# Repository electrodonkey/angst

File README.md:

# ANGST - Angle seNsor Gimbal SysTem

## Master thesis project in Advanced Microelectronics

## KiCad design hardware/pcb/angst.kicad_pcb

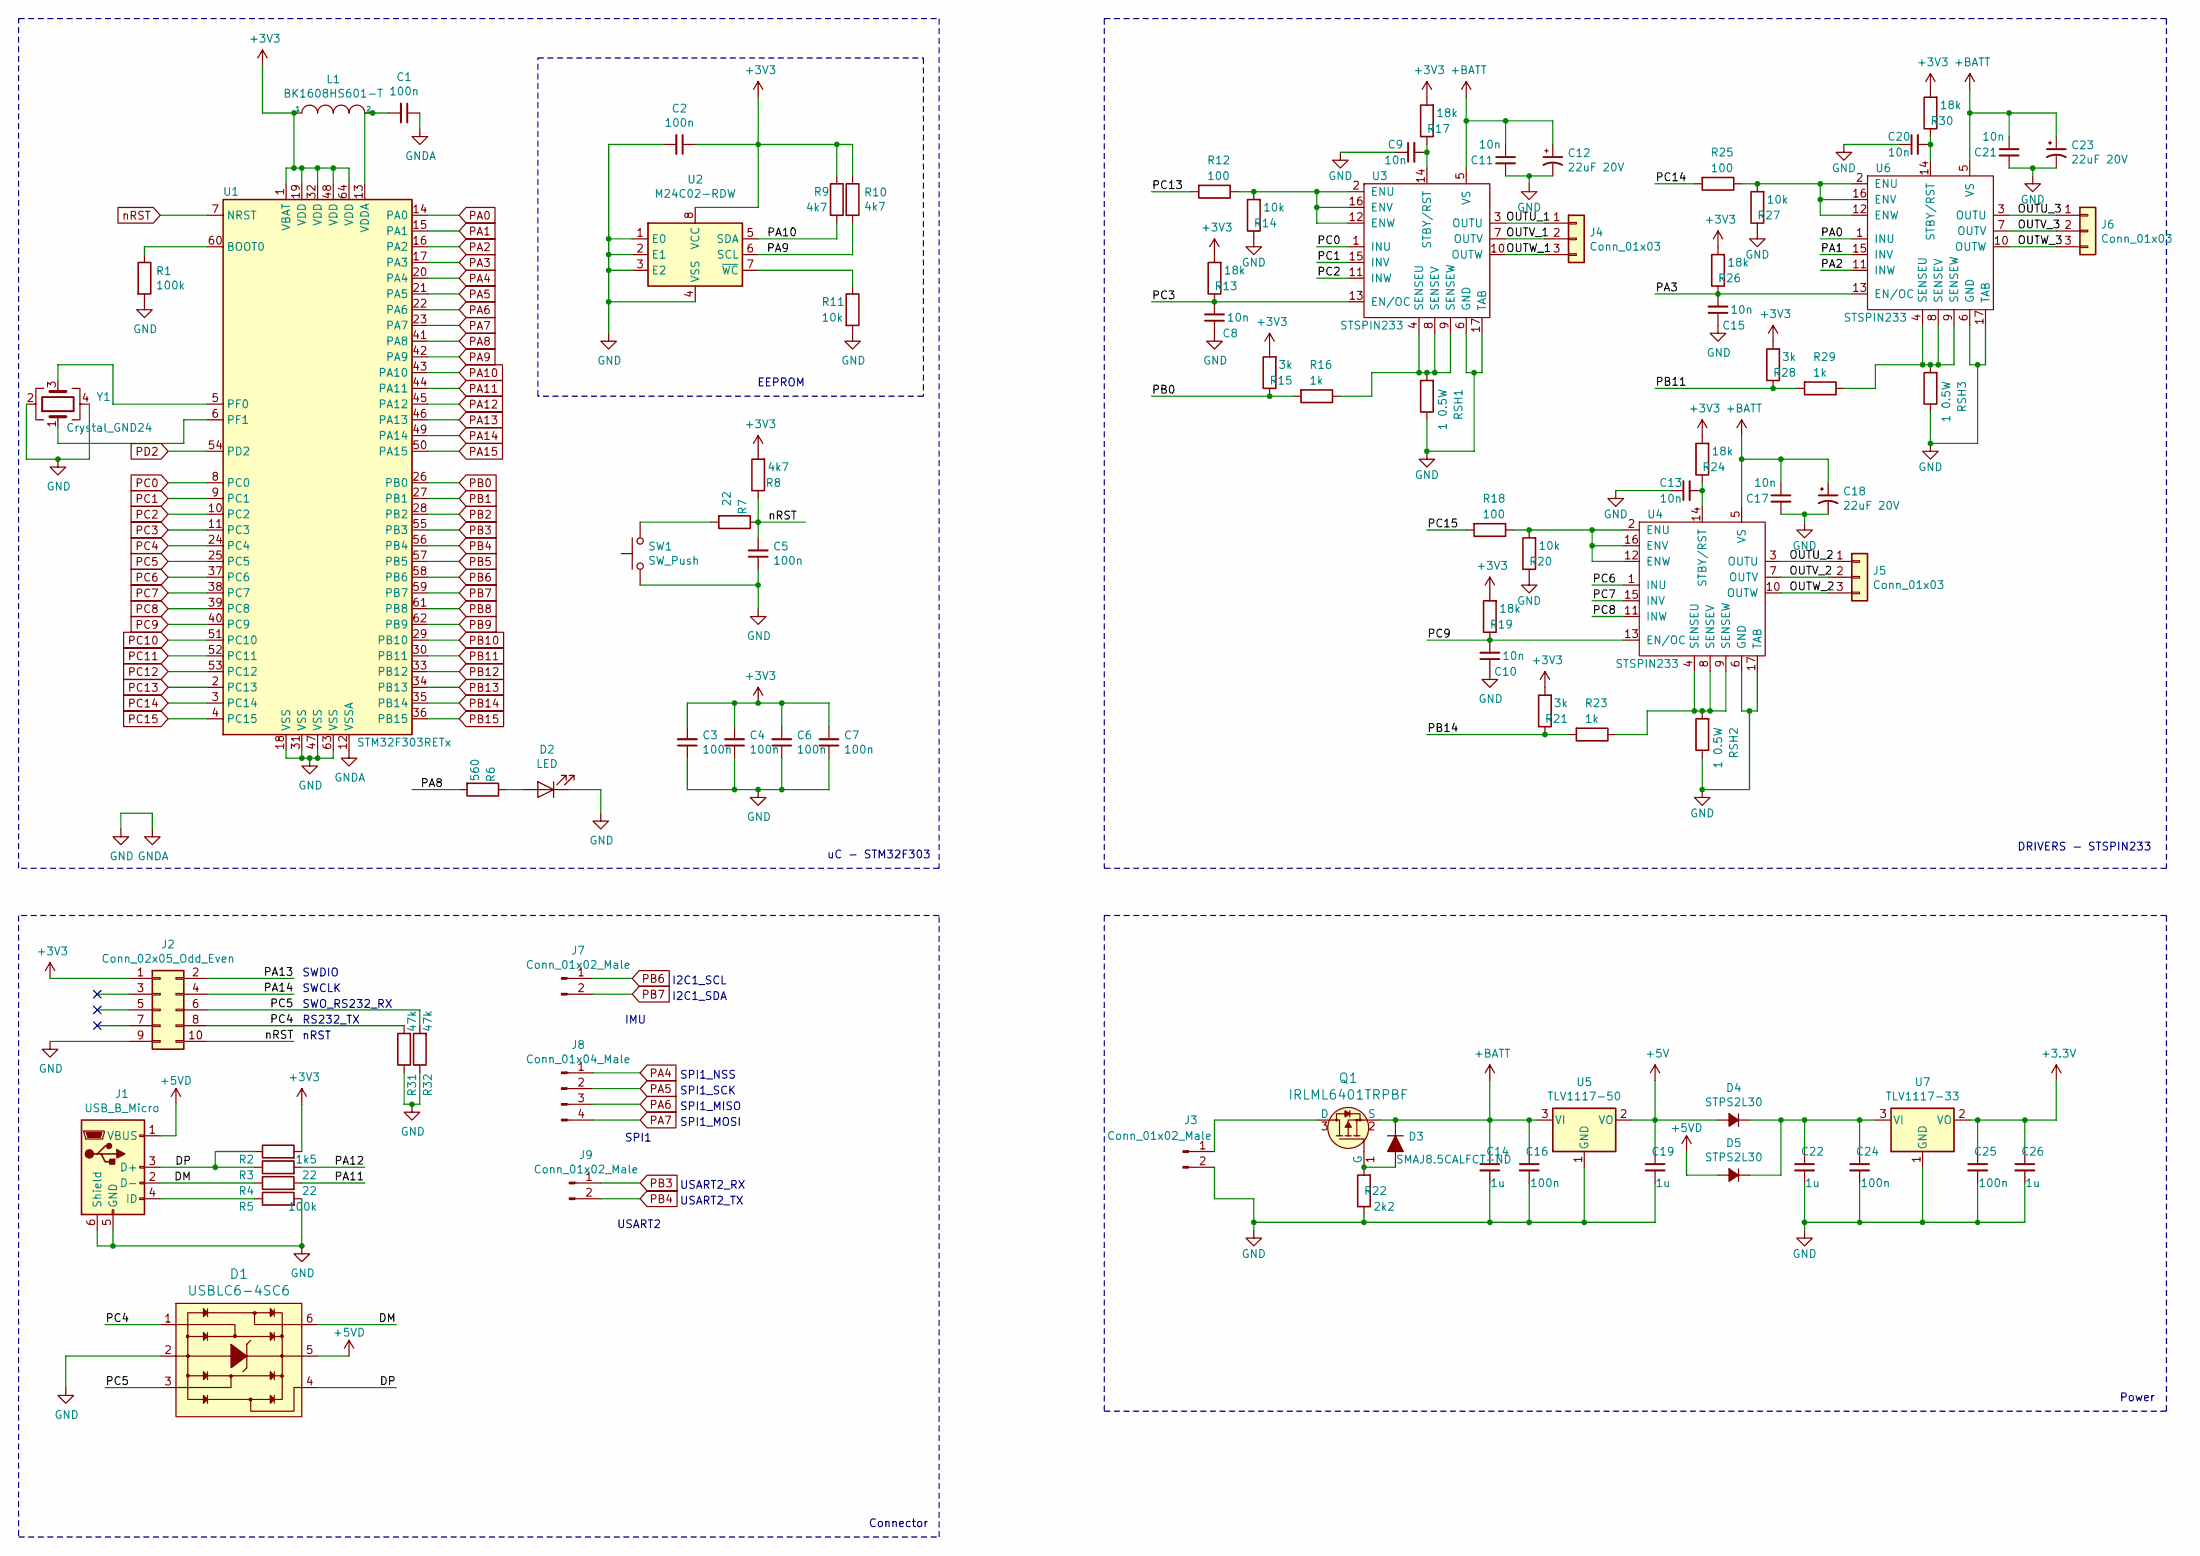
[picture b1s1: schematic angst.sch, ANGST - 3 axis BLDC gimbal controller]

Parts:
C1, C2, C3, C4, C5, C6, C7, C16, C24, C25: 100n; C_0603_1608Metric_Pad1.05x0.95mm_HandSolder
C8, C9, C10, C11, C13, C15, C17, C20, C21: 10n; C_0603_1608Metric_Pad1.05x0.95mm_HandSolder
C12, C18, C23: 22uF 20V; CP_EIA-1608-08_AVX-J_Pad1.25x1.05mm_HandSolder
C14, C19, C22, C26: 1u; C_0603_1608Metric_Pad1.05x0.95mm_HandSolder
D1: USBLC6-4SC6; SOT23-6L; MPN USBLC6-4SC6; Digi-Key_PN 497-4492-1-ND
D2: LED; LED_0603_1608Metric_Pad1.05x0.95mm_HandSolder
D3: SMAJ8.5CALFCT-ND; D_SMA
D4, D5: STPS2L30; D_SMA
J1: USB_B_Micro; USB_Micro-B_Molex-105017-0001
J2: Conn_02x05_Odd_Even; Harwin_Gecko-G125-FVX1005L0X_2x05_P1.25mm_Vertical
J3, J7, J9: Conn_01x02_Male; JST_EH_B2B-EH-A_1x02_P2.50mm_Vertical
J4, J5, J6: Conn_01x03; JST_EH_B3B-EH-A_1x03_P2.50mm_Vertical
J8: Conn_01x04_Male; JST_EH_B4B-EH-A_1x04_P2.50mm_Vertical
L1: BK1608HS601-T; L_0603_1608Metric_Pad1.05x0.95mm_HandSolder
Q1: IRLML6401TRPBF; SOT-23-3; MPN IRLML6401TRPBF; Digi-Key_PN IRLML6401PBFCT-ND
R1, R5: 100k; R_0603_1608Metric_Pad1.05x0.95mm_HandSolder
R2: 1k5; R_0603_1608Metric_Pad1.05x0.95mm_HandSolder
R3, R4, R7: 22; R_0603_1608Metric_Pad1.05x0.95mm_HandSolder
R6: 560; R_0603_1608Metric_Pad1.05x0.95mm_HandSolder
R8, R9, R10: 4k7; R_0603_1608Metric_Pad1.05x0.95mm_HandSolder
R11, R14, R20, R27: 10k; R_0603_1608Metric_Pad1.05x0.95mm_HandSolder
R12, R18, R25: 100; R_0603_1608Metric_Pad1.05x0.95mm_HandSolder
R13, R17, R19, R24, R26, R30: 18k; R_0603_1608Metric_Pad1.05x0.95mm_HandSolder
R15, R21, R28: 3k; R_0603_1608Metric_Pad1.05x0.95mm_HandSolder
R16, R23, R29: 1k; R_0603_1608Metric_Pad1.05x0.95mm_HandSolder
R22: 2k2; R_0603_1608Metric_Pad1.05x0.95mm_HandSolder
R31, R32: 47k; R_0603_1608Metric_Pad1.05x0.95mm_HandSolder
RSH1, RSH2, RSH3: 1 0.5W; R_1206_3216Metric_Pad1.42x1.75mm_HandSolder
SW1: SW_Push; SW_SPST_EVPBF
U1: STM32F303RETx; LQFP-64_10x10mm_P0.5mm
U2: M24C02-RDW; TSSOP-8_4.4x3mm_P0.65mm
U3, U4, U6: STSPIN233; VFQFN-16-1EP_3x3mm
U5: TLV1117-50; SOT-223
U7: TLV1117-33; SOT-223
Y1: Crystal_GND24; Crystal_SMD_0603-4Pin_6.0x3.5mm_HandSoldering

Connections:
+5V: C19.1, D4.2 (A), U5.2 (VO)
+5VD: D1.5, D5.2 (A), J1.1 (VBUS)
+BATT: C11.1, C12.1, C14.1, C16.1, C17.1, C18.1, C21.1, C23.1, D3.1 (K), Q1.2 (S), U3.5 (VS), U4.5 (VS), U5.3 (VI), U6.5 (VS)
/DM: D1.6, J1.2 (D-), R4.1
/DP: D1.4, J1.3 (D+), R2.1, R3.1
/OUTU_1: J4.1, U3.3 (OUTU)
/OUTU_2: J5.1, U4.3 (OUTU)
/OUTU_3: J6.1, U6.3 (OUTU)
/OUTV_1: J4.2, U3.7 (OUTV)
/OUTV_2: J5.2, U4.7 (OUTV)
/OUTV_3: J6.2, U6.7 (OUTV)
/OUTW_1: J4.3, U3.10 (OUTW)
/OUTW_2: J5.3, U4.10 (OUTW)
/OUTW_3: J6.3, U6.10 (OUTW)
GND: C1.1, C2.2, C3.1, C4.1, C5.1, C6.1, C7.1, C8.1, C9.1, C10.1, C11.2, C12.2, C13.1, C14.2, C15.1, C16.2, C17.2, C18.2, C19.2, C20.1, C21.2, C22.2, C23.2, C24.2, C25.2, C26.2, D1.2, D2.1 (K), J1.5 (GND), J1.6 (Shield), J2.9, J3.2, R1.2, R5.2, R11.2, R14.1, R20.1, R22.1, R27.1, R31.1, R32.1, RSH1.1, RSH2.1, RSH3.1, SW1.1, U1.12 (VSSA), U1.18 (VSS), U1.31 (VSS), U1.47 (VSS), U1.63 (VSS), U2.1 (E0), U2.2 (E1), U2.3 (E2), U2.4 (VSS), U3.6 (GND), U3.17 (TAB), U4.6 (GND), U4.17 (TAB), U5.1 (GND), U6.6 (GND), U6.17 (TAB), U7.1 (GND), Y1.2, Y1.4
unnamed: C1.2, L1.2, U1.13 (VDDA)
unnamed: C9.2, R17.1, U3.14 (STBY/RST)
unnamed: C13.2, R24.1, U4.14 (STBY/RST)
unnamed: C20.2, R30.1, U6.14 (STBY/RST)
unnamed: C22.1, C24.1, D4.1 (K), D5.1 (K), U7.3 (VI)
unnamed: D2.2 (A), R6.1
unnamed: D3.2 (A), Q1.1 (G), R22.2
unnamed: J1.4 (ID), R5.1
unnamed: J3.1, Q1.3 (D)
unnamed: R1.1, U1.60 (BOOT0)
unnamed: R7.2, SW1.2
unnamed: R11.1, U2.7 (~WC)
unnamed: R12.1, R14.2, U3.2 (ENU), U3.12 (ENW), U3.16 (ENV)
unnamed: R16.1, RSH1.2, U3.4 (SENSEU), U3.8 (SENSEV), U3.9 (SENSEW)
unnamed: R18.1, R20.2, U4.2 (ENU), U4.12 (ENW), U4.16 (ENV)
unnamed: R23.1, RSH2.2, U4.4 (SENSEU), U4.8 (SENSEV), U4.9 (SENSEW)
unnamed: R25.1, R27.2, U6.2 (ENU), U6.12 (ENW), U6.16 (ENV)
unnamed: R29.1, RSH3.2, U6.4 (SENSEU), U6.8 (SENSEV), U6.9 (SENSEW)
unnamed: U1.5 (PF0), Y1.3
unnamed: U1.6 (PF1), Y1.1
PA0: U1.14 (PA0), U6.1 (INU)
PA1: U1.15 (PA1), U6.15 (INV)
PA2: U1.16 (PA2), U6.11 (INW)
PA3: C15.2, R26.1, U1.17 (PA3), U6.13 (EN/OC)
PA4: J8.1, U1.20 (PA4)
PA5: J8.2, U1.21 (PA5)
PA6: J8.3, U1.22 (PA6)
PA7: J8.4, U1.23 (PA7)
PA8: R6.2, U1.41 (PA8)
PA9: R10.2, U1.42 (PA9), U2.6 (SCL)
PA10: R9.2, U1.43 (PA10), U2.5 (SDA)
PA11: R4.2, U1.44 (PA11)
PA12: R3.2, U1.45 (PA12)
PA13: J2.2, U1.46 (PA13)
PA14: J2.4, U1.49 (PA14)
PA15: U1.50 (PA15)
PB0: R15.1, R16.2, U1.26 (PB0)
PB1: U1.27 (PB1)
PB2: U1.28 (PB2)
PB3: J9.1, U1.55 (PB3)
PB4: J9.2, U1.56 (PB4)
PB5: U1.57 (PB5)
PB6: J7.1, U1.58 (PB6)
PB7: J7.2, U1.59 (PB7)
PB8: U1.61 (PB8)
PB9: U1.62 (PB9)
PB10: U1.29 (PB10)
PB11: R28.1, R29.2, U1.30 (PB11)
PB12: U1.33 (PB12)
PB13: U1.34 (PB13)
PB14: R21.1, R23.2, U1.35 (PB14)
PB15: U1.36 (PB15)
PC0: U1.8 (PC0), U3.1 (INU)
PC1: U1.9 (PC1), U3.15 (INV)
PC2: U1.10 (PC2), U3.11 (INW)
PC3: C8.2, R13.1, U1.11 (PC3), U3.13 (EN/OC)
PC4: D1.1, J2.8, R31.2, U1.24 (PC4)
PC5: D1.3, J2.6, R32.2, U1.25 (PC5)
PC6: U1.37 (PC6), U4.1 (INU)
PC7: U1.38 (PC7), U4.15 (INV)
PC8: U1.39 (PC8), U4.11 (INW)
PC9: C10.2, R19.1, U1.40 (PC9), U4.13 (EN/OC)
PC10: U1.51 (PC10)
PC11: U1.52 (PC11)
PC12: U1.53 (PC12)
PC13: R12.2, U1.2 (PC13)
PC14: R25.2, U1.3 (PC14)
PC15: R18.2, U1.4 (PC15)
PD2: U1.54 (PD2)
nRST: C5.2, J2.10, R7.1, R8.1, U1.7 (NRST)

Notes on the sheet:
EEPROM
uC - STM32F303
DRIVERS - STSPIN233
Power
SWDIO
SWCLK
SWO_RS232_RX
RS232_TX
nRST
I2C1_SCL
I2C1_SDA
IMU
SPI1_NSS
SPI1_SCK
SPI1_MISO
SPI1_MOSI
USART2_RX
USART2_TX
USART2
SPI1
Connector

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
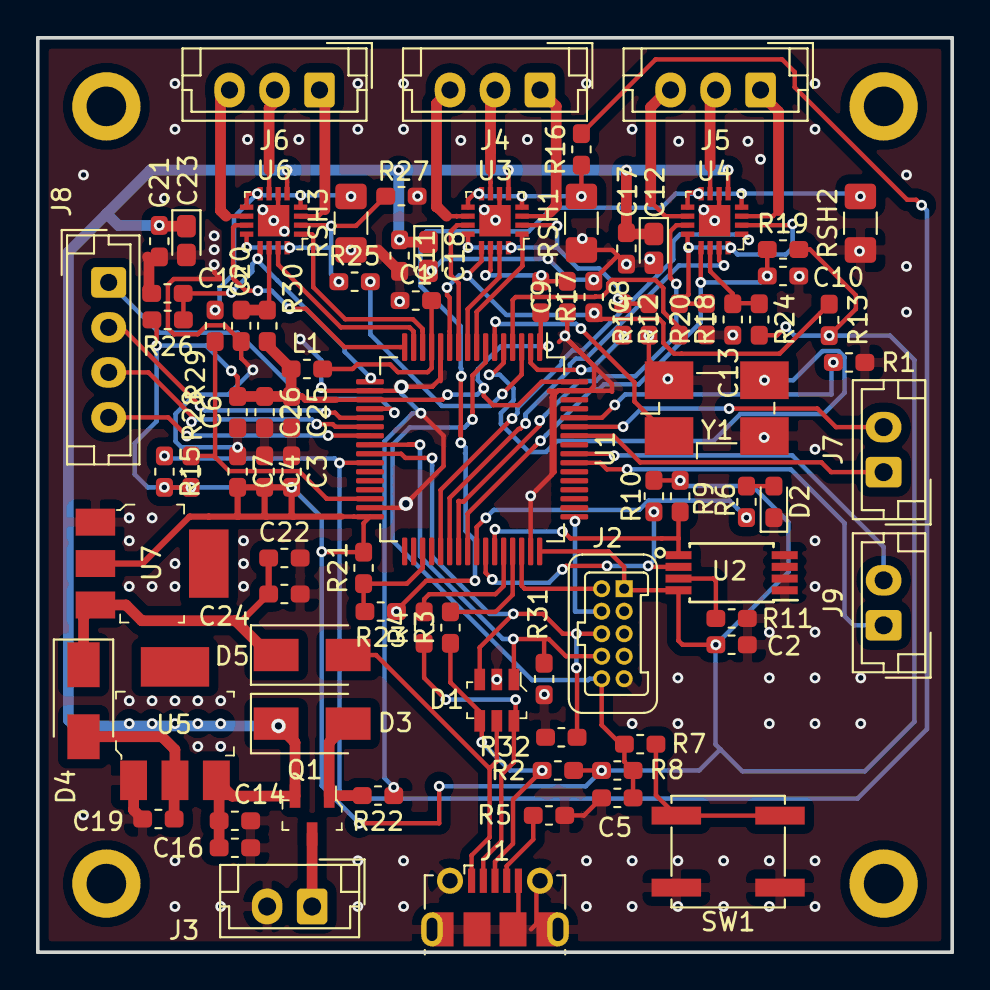
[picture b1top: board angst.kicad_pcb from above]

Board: 2 copper layers, 50.8 x 50.8 mm, 86 parts (0 on the bottom side), 72 nets.

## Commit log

2019-04-15 Add initial KiCad files
2019-04-15 Finish work on MCU block, start work on driver block
2019-04-15 Add motor driver block and connector block.
2019-04-16 Add power block
2019-04-18 Clean up power concept. Add connector block
2019-04-18 Removed Driver_Motor, unused lib
2019-04-18 Add bead footprint
2019-04-18 Add pin assigment file for STM32 uC
2019-04-19 Add stm32 datasheet
2019-04-19 Start work on PCB layout
2019-04-19 Add initial placement of components on layout
2019-04-19 Add info about project
2019-04-20 Continue work on power block layout
2019-04-23 Add work on drivers
2019-04-25 Continue layout
2019-04-25 Ratnest finished, start arranging graphics
2019-04-25 Work on layout
2019-04-26 Finish layout and board art. V1.0 production ready
2019-04-26 Add schematic.pdf
2019-04-26 Add part list
2019-04-26 Update shopping list
2019-05-02 Clean up BOM
